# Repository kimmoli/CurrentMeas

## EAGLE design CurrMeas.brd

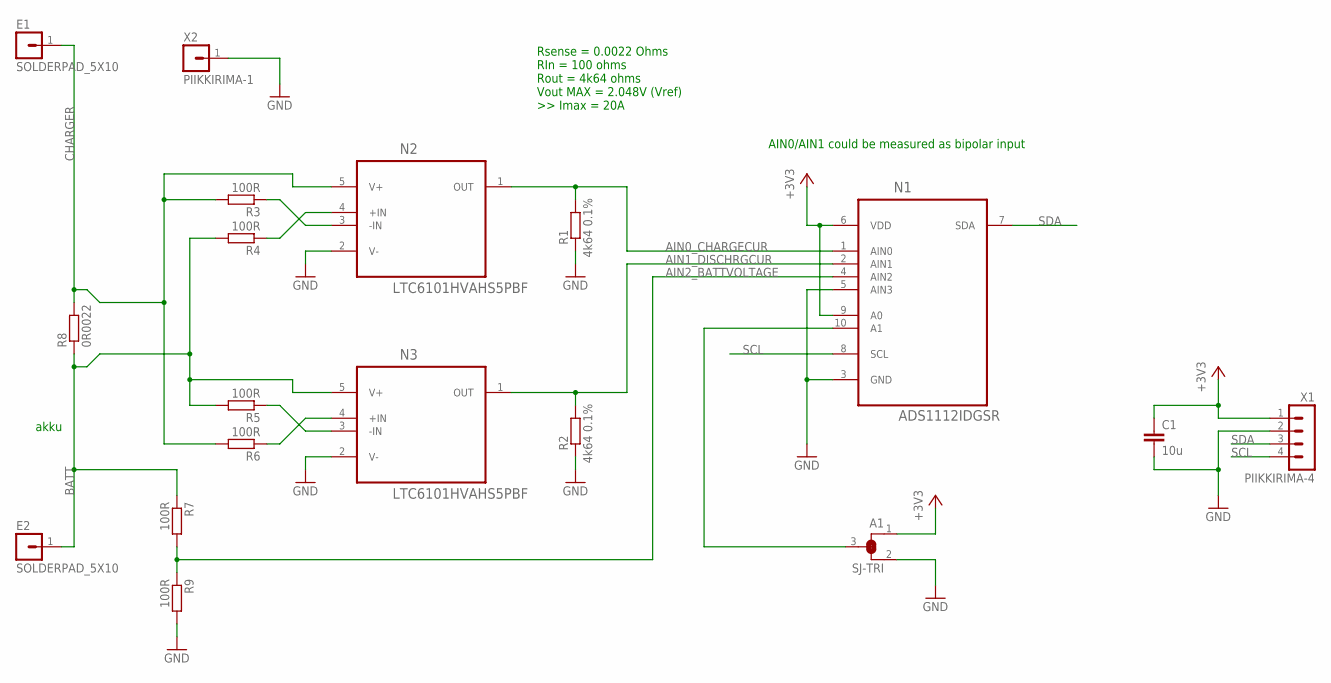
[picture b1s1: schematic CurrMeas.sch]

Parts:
A1: SJ-TRI; SJ-SMALL-TRI
C1: 10u; C0805
E1, E2: SOLDERPAD_5X10
N1: ADS1112IDGSR; SOP50P490X110-10N
N2, N3: LTC6101HVAHS5PBF; SOT95P280X100-5N
R1, R2: 4k64 0.1%; R0603
R3, R4, R5, R6, R7, R9: 100R; R0603
R8: 0R0022; R2512
X1: PIIKKIRIMA-4
X2: PIIKKIRIMA-1

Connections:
+3V3: A1.1, C1.1, N1.6 (VDD), N1.9 (A0), X1.1
AIN0_CHARGECUR: N1.1 (AIN0), N2.1 (OUT), R1.2
AIN1_DISCHRGCUR: N1.2 (AIN1), N3.1 (OUT), R2.2
AIN2_BATTVOLTAGE: N1.4 (AIN2), R7.2, R9.1
BATT: E2.1, N3.5 (V+), R4.2, R5.2, R7.1, R8.1
CHARGER: E1.1, N2.5 (V+), R3.2, R6.2, R8.2
GND: A1.2, C1.2, N1.3 (GND), N1.5 (AIN3), N2.2 (V-), N3.2 (V-), R1.1, R2.1, R9.2, X1.2, X2.1
unnamed: A1.3, N1.10 (A1)
unnamed: N2.3 (-IN), R3.1
unnamed: N2.4 (+IN), R4.1
unnamed: N3.4 (+IN), R6.1
unnamed: N3.3 (-IN), R5.1
SCL: N1.8 (SCL), X1.4
SDA: N1.7 (SDA), X1.3

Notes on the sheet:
Rsense = 0.0022 Ohms RIn = 100 ohms Rout = 4k64 ohms Vout MAX = 2.048V (Vref) >> Imax = 20A
AIN0/AIN1 could be measured as bipolar input
akku

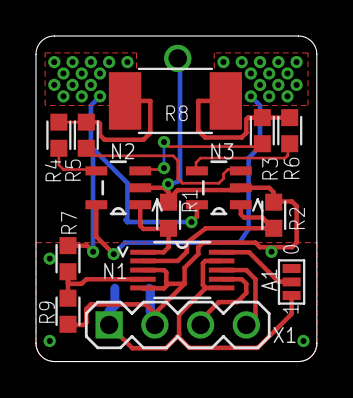
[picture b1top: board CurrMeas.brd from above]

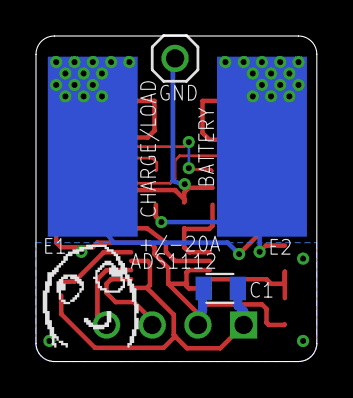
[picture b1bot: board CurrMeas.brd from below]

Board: 2 copper layers, 15.6 x 18.1 mm, 19 parts (5 on the bottom side), 14 nets.

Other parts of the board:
U$1: DAFUG

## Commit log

2013-09-14 Excel with some information added
    luonnostelua !
